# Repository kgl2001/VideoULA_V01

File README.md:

# VideoULA V01 — BBC Micro Video ULA Replacement
## 44-pin Xilinx XC9572XL CPLD Version

This repository contains the hardware design and firmware for the VideoULA V01, a drop-in replacement for the VC2069 Video ULA (IC6) in the Acorn BBC Micro Model B.

---

## Project Overview

The original BBC Micro Video ULA (IC6) is a custom ASIC that is no longer manufactured. Failed or missing ULAs result in a non-functional machine. This project provides a modern replacement using a CPLD and a small external SRAM for palette storage.

There are three hardware versions of this replacement, each in a separate repository:

| Version | CPLD | Macrocells | Tool | Repository |
|---|---|---|---|---|
| **V01** | Xilinx XC9572XL-10-VQ44 | 72 | ISE 14.7 | This repo |
| V02 | Xilinx XC9572XL-10-VQ64 | 72 | ISE 14.7 | [VideoULA_V02](https://github.com/kgl2001/VideoULA_V02) |
| V03 | Atmel ATF1504AS-10AU44 | 64 | Quartus 13.0 SP1 | [VideoULA_V03](https://github.com/kgl2001/VideoULA_V03) |

All three versions share the same 28-pin DIP footprint as the original ULA and are pin-compatible with the BBC Micro motherboard.

---

## V01 Hardware

- **CPLD**: Xilinx XC9572XL-10-VQ44 (72 macrocells, 3.3V core, 5V tolerant I/O)
- **SRAM**: ISSI IS62C256AL-45TLI (32K×8, 5V, TSOP-28, 45ns) — only locations 0-15 and bits 0-3 used
- **Oscillator**: 48MHz SMD oscillator (3225 package, 5V) — for 48MHz operating mode only
- **LDO**: XC6206P332MR (SOT-23, 3.3V) — powers CPLD core

### Hardware Revisions

| Revision | Status | Changes |
|---|---|---|
| Rev01 | Built and tested | Initial release |
| Rev02 | PCB designed, not yet built | Added 47Ω series resistor and 74LVC1G17 Schmitt trigger buffer on CLK_IN; CPLD pin assignments updated |
| Rev03 | PCB designed, not yet built | Added 74LV6T17 to buffer all clock outputs (8/4/2/1MHz, CRTC) for Master 128 compatibility |
| Rev04 | PCB designed, not yet built | Repositioned JTAG header |

Note: Only Rev01 has been built and tested. Rev02 onwards incorporate improvements identified during Rev01 testing.

### CLK_IN Reliability Daughterboard

During testing of Rev01 on BBC Micro machines with the original 16MHz clock circuit, some machines showed reliability issues in 16MHz operating mode — particularly on cold startup. Investigation revealed that the BBC's 16MHz crystal oscillator circuit produces a noisy clock signal that the CPLD occasionally misinterprets as spurious edges, causing display glitches.

To address this without waiting for a new PCB revision, a small standalone buffer board was developed. This daughterboard:

- Plugs into the BBC Micro motherboard in place of the VideoULA V01
- The VideoULA V01 then plugs into the daughterboard
- Intercepts the 16MHz clock signal from the BBC motherboard
- Passes it through a 47Ω series resistor and 74HCT14E Schmitt trigger buffer before it reaches the CPLD
- Passes all other signals through unchanged

The 74HCT14E was chosen as a through-hole part for ease of hand soldering. Rev02+ PCB designs use the smaller surface-mount 74LVC1G17 in conjunction with a series resistor to achieve the same signal conditioning in a more compact form.

This fix was confirmed to resolve the cold startup reliability issues on affected machines. The improvement has been incorporated into Rev02 of the V01 PCB and all subsequent hardware versions.

The daughterboard design files are included in this repository.

---

## Firmware

The firmware is written in Verilog and built using Xilinx ISE 14.7.

### Operating Modes

Two firmware builds are required — one per operating mode. To switch modes, reprogram the CPLD with the appropriate `.jed` file. A solder bridge on the PCB selects whether the 48MHz oscillator or the BBC's 16MHz clock is connected to the CPLD clock input.

#### 48MHz Mode (recommended)
- Uses the onboard 48MHz oscillator as the master clock
- Generates all BBC clock outputs (8/4/2/1MHz, CRTC, 6MHz) internally
- Provides clean, phase-locked 6MHz output for the SAA5050 teletext chip (tD ≈ 20ns ✓)
- Works reliably on all machines from cold power-up, including those with noisy clock circuits
- Build: uncomment `` `define CLK_48MHZ `` in `VideoULA.v`

#### 16MHz Mode
- Uses the BBC motherboard's 16MHz clock as the master clock
- No onboard oscillator required
- May show brief display noise on cold startup on machines with noisy 16MHz clock circuits
- The CLK_IN daughterboard resolves this on Rev01; Rev02+ has the fix built in
- Build: uncomment `` `define CLK_16MHZ `` in `VideoULA.v`

### ISE Fitter Settings (critical)

| Setting | Value | Notes |
|---|---|---|
| Implementation Template | **Optimise Speed** | Density causes timing failures at temperature |
| Macrocell Power | **Std** | Low Power prevents BBC from booting |
| Output Slew Rate | Fast | |
| Default Powerup Value | Low | |
| Pterms | **14** (16MHz build only) | Default 25 causes silent fit failure in 16MHz build |

### Build Instructions

1. Open Xilinx ISE 14.7
2. Create a new project targeting `XC9572XL-10-VQ44`
3. Add `src/VideoULA.v` and `src/VideoULA.ucf` to the project
4. Select the operating mode by uncommenting the appropriate `define` in `VideoULA.v`
5. Set fitter options as above
6. Run `Implement Design` to generate the `.jed` file
7. Program the CPLD using iMPACT or a compatible JTAG programmer

---

## SRAM Wiring

The external SRAM stores the 16-entry colour palette (4 bits per entry):

| SRAM Pin | Connection |
|---|---|
| A0-A3 | CPLD SRAM_ADDR[0:3] |
| A4-A14 | GND (tie low) |
| D0-D3 | CPLD SRAM_DATA[0:3] (bidirectional) |
| D4-D7 | Leave unconnected |
| /WE | CPLD SRAM_nWE |
| /OE | GND (always output enabled) |
| /CS | GND (always selected) |

---

## 6MHz Clock for Mode 7 (Teletext)

The SAA5050 teletext chip requires a 6MHz clock with a specific phase relationship to the 1MHz system clock (tD = 6-60ns from 6MHz rising edge to 1MHz falling edge).

- **48MHz mode**: The CPLD generates a clean, phase-locked 6MHz output on the CLK_6M pin (tD ≈ 20ns ✓). This can be connected to the SAA5050 via an IC37 replacement board.
- **16MHz mode**: The BBC motherboard's existing 6MHz generation circuit is used. The CPLD CLK_6M output is held high-Z.

---

## PCB Design Notes

The PCB has been designed using KiCAD V10 as a 2-layer board. It can easily be changed to a 4-layer board with GND/Power planes on the inner layers if signal integrity is a concern.

### JLCPCB Fabrication

The board design includes a 5×5mm silkscreen box on the underside of the PCB. This is used by JLCPCB to position a QR code serial number. When ordering from JLCPCB:

- Select **Specify position** in the QR code / 2D barcode options during the ordering process
- If this option is not selected, JLCPCB will print the 5×5mm silkscreen box as-is and attempt to place the QR code at a different location of their choosing

If not using JLCPCB, the chosen fabricator will likely print the 5×5mm box as a plain white square on the PCB. To avoid this, remove the silkscreen box from the PCB design and regenerate the Gerber files before submitting.

### Assembly

A combined CPL (Component Placement List) and BOM (Bill of Materials) Excel file is included in the Gerbers folder. This can be used directly with the JLCPCB PCBA (PCB Assembly) service.

Note that the JLCPCB Economy PCBA process only assembles components on one side of the PCB. Select the **top side** for assembly — this leaves only the SRAM and its associated decoupling capacitor to be hand soldered to the underside of the board.

---

## Known Limitations

- **Cold startup noise (16MHz mode, standard clock machines)**: Machines with noisy 16MHz clock circuits may show brief display noise on cold power-up. Use the CLK_IN daughterboard (Rev01) or upgrade to Rev02+ which has the fix built in. The 48MHz operating mode is not affected.
- **Master 128 compatibility**: V01 has not been tested on the Master 128. Clock output buffering (added in Rev03) may be required for full Master 128 compatibility.
- **SCART/HDMI adapter compatibility**: Some SCART→HDMI display adapters may show minor pixel artefacts with non-standard screen modes. RGBtoHDMI and direct CRT connections are not affected.

---

## Compatibility

Tested on BBC Micro Model B with original clock circuit and with clock fixer modification. Not tested on BBC Master 128.

---

## Credits

- **Ken Lowe** — PCB design, Verilog development and testing
- **hoglet (Stardot forums)** — Clock architecture analysis, DRAM timing analysis, community testing
- **Stardot community** — Testing, feedback and suggestions

---

## Licence

Hardware: [Creative Commons BY-SA 4.0](https://creativecommons.org/licenses/by-sa/4.0/)

Firmware: [MIT Licence](https://opensource.org/licenses/MIT)

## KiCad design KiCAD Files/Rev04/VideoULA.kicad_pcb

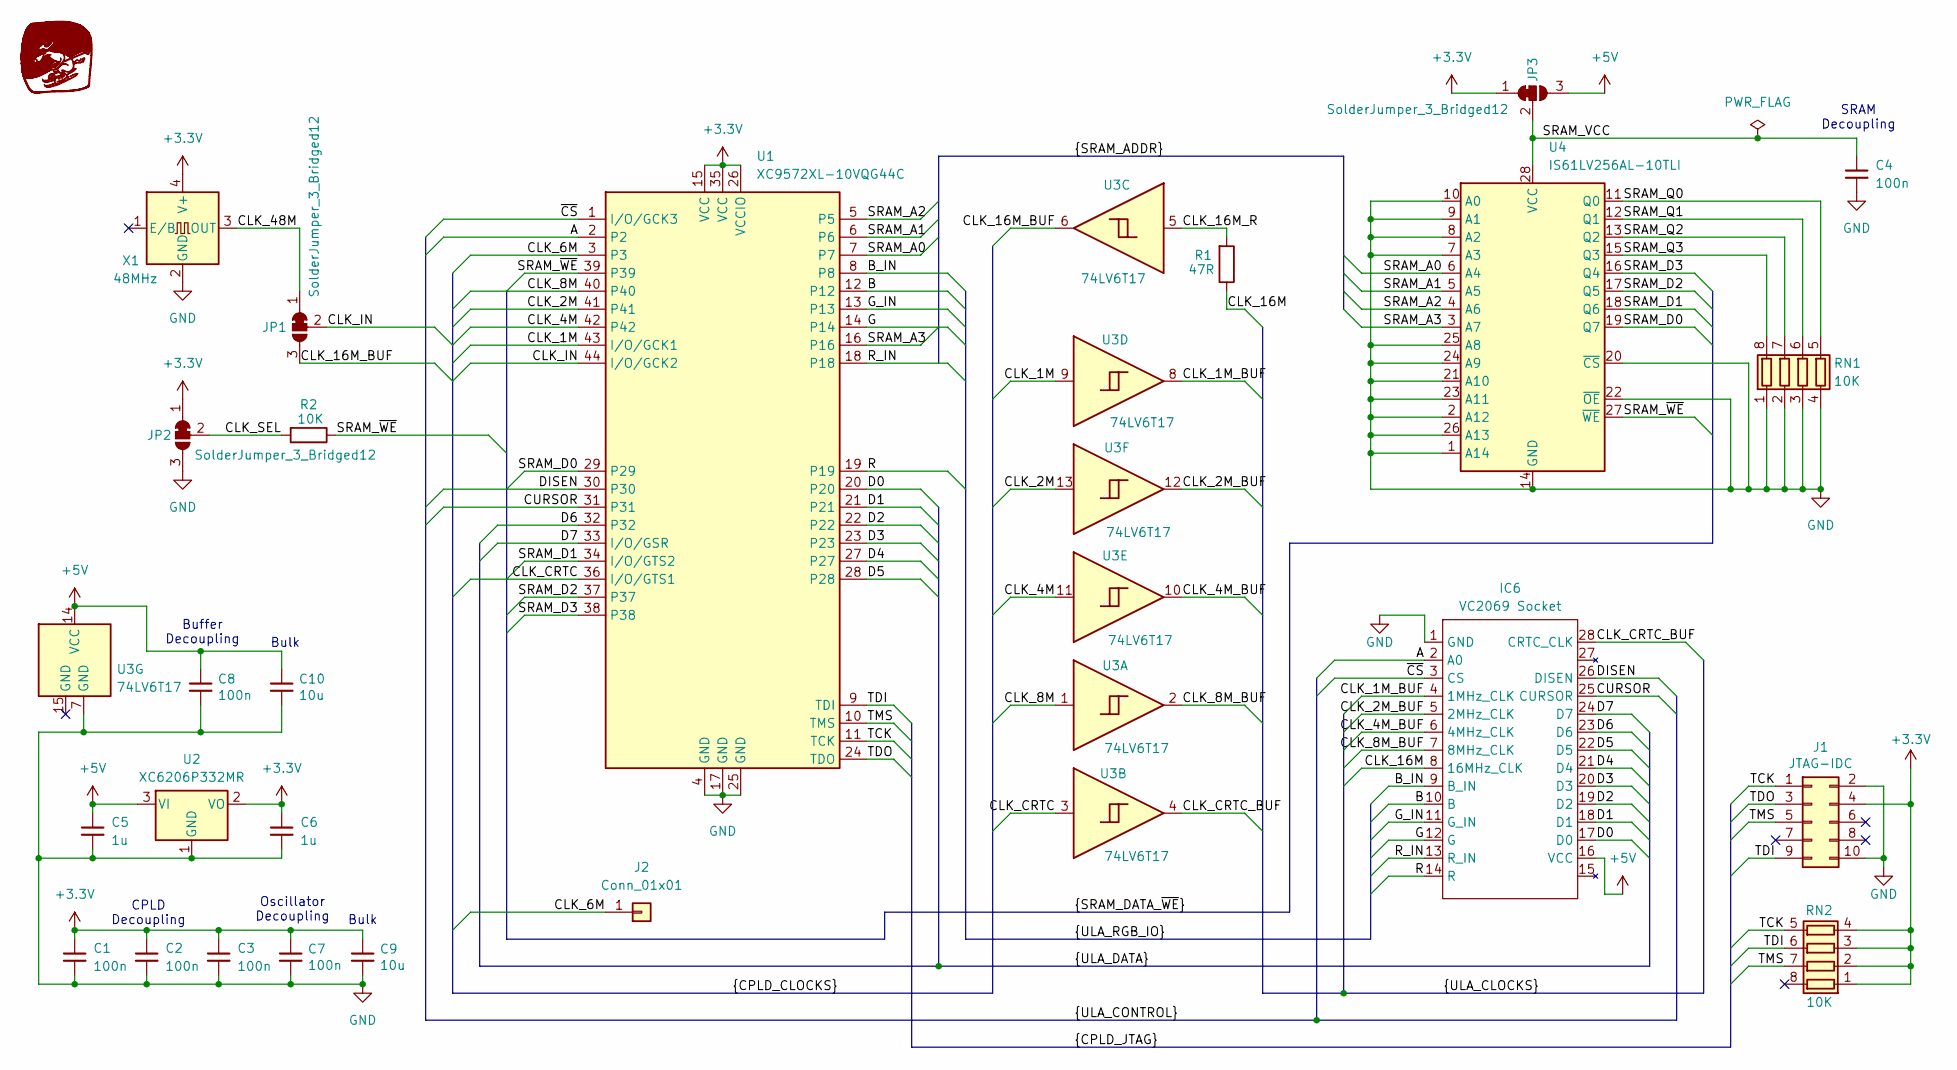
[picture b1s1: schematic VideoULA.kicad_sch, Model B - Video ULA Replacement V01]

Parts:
C1, C2, C3, C4, C7, C8: 100n; C_0603_1608Metric; JLC Part Number C14663
C5, C6: 1u; C_0603_1608Metric; JLC Part Number C15849
C9, C10: 10u; C_0603_1608Metric; JLC Part Number C19702
G1: Skidog; skidog_inv
IC6: VC2069 Socket; DIP-28_W15.24mm
J1: JTAG-IDC; PinHeader_2x05_P2.54mm_Vertical
J2: Conn_01x01; PinHeader_1x01_P2.54mm_Horizontal
JP1, JP2, JP3: SolderJumper_3_Bridged12; SolderJumper-3_P1.3mm_Bridged12_RoundedPad1.0x1.5mm
R1: 47R; R_0603_1608Metric; JLC Part Number C23182
R2: 10K; R_0603_1608Metric; JLC Part Number C25804
RN1, RN2: 10K; R_Array_Convex_4x0603; JLC Part Number C29718
U1: XC9572XL-10VQG44C; LQFP-44_10x10mm_P0.8mm; JLC Part Number C569042
U2: XC6206P332MR; SOT-23-3; JLC Part Number C5446
U3: 74LV6T17; DHWQFN-14-1EP_2.5x3mm_P0.5mm_EP1x1.5mm_ThermalVias; JLC Part Number C22428345
U4: IS61LV256AL-10TLI; TSOP-I-28_11.8x8mm_P0.55mm_SRAM; JLC Part Number C2062662
X1: 48MHz; Oscillator_SMD_Yajingxin_TFOM48M4RHKCNT2T-4Pin_3.2x2.5mm; JLC Part Number C454614

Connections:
+3.3V: C1.1, C2.1, C3.1, C6.1, C7.1, C9.1, J1.4, JP2.1 (A), JP3.1 (A), RN2.1 (R1.1), RN2.2 (R2.1), RN2.3 (R3.1), RN2.4 (R4.1), U1.15 (VCC), U1.26 (VCCIO), U1.35 (VCC), U2.2 (VO), X1.4 (V+)
+5V: C5.1, C8.1, C10.1, IC6.16 (VCC), JP3.3 (B), U2.3 (VI), U3.14 (VCC)
/A: IC6.2 (A0), U1.2
/B: IC6.10 (B), U1.12
/B_IN: IC6.9 (B_IN), U1.8
/CLK_1M: U1.43 (I/O/GCK1), U3.9
/CLK_1M_BUF: IC6.4 (1MHz_CLK), U3.8
/CLK_2M: U1.41, U3.13
/CLK_2M_BUF: IC6.5 (2MHz_CLK), U3.12
/CLK_4M: U1.42, U3.11
/CLK_4M_BUF: IC6.6 (4MHz_CLK), U3.10
/CLK_6M: J2.1 (Pin_1_1), U1.3
/CLK_8M: U1.40, U3.1
/CLK_8M_BUF: IC6.7 (8MHz_CLK), U3.2
/CLK_16M: IC6.8 (16MHz_CLK), R1.1
/CLK_16M_BUF: JP1.3 (B), U3.6
/CLK_16M_R: R1.2, U3.5
/CLK_48M: JP1.1 (A), X1.3 (OUT)
/CLK_CRTC: U1.36 (I/O/GTS1), U3.3
/CLK_CRTC_BUF: IC6.28 (CRTC_CLK), U3.4
/CLK_IN: JP1.2 (C), U1.44 (I/O/GCK2)
/CLK_SEL: JP2.2 (C), R2.2
/CURSOR: IC6.25 (CURSOR), U1.31
/D0: IC6.17 (D0), U1.20
/D1: IC6.18 (D1), U1.21
/D2: IC6.19 (D2), U1.22
/D3: IC6.20 (D3), U1.23
/D4: IC6.21 (D4), U1.27
/D5: IC6.22 (D5), U1.28
/D6: IC6.23 (D6), U1.32
/D7: IC6.24 (D7), U1.33 (I/O/GSR)
/DISEN: IC6.26 (DISEN), U1.30
/G: IC6.12 (G), U1.14
/G_IN: IC6.11 (G_IN), U1.13
/R: IC6.14 (R), U1.19
/R_IN: IC6.13 (R_IN), U1.18
/SRAM_A0: U1.7, U4.6 (A4)
/SRAM_A1: U1.6, U4.5 (A5)
/SRAM_A2: U1.5, U4.4 (A6)
/SRAM_A3: U1.16, U4.3 (A7)
/SRAM_D0: U1.29, U4.19 (Q7)
/SRAM_D1: U1.34 (I/O/GTS2), U4.18 (Q6)
/SRAM_D2: U1.37, U4.17 (Q5)
/SRAM_D3: U1.38, U4.16 (Q4)
/SRAM_Q0: RN1.5 (R4.2), U4.11 (Q0)
/SRAM_Q1: RN1.6 (R3.2), U4.12 (Q1)
/SRAM_Q2: RN1.7 (R2.2), U4.13 (Q2)
/SRAM_Q3: RN1.8 (R1.2), U4.15 (Q3)
/SRAM_VCC: C4.1, JP3.2 (C), U4.28 (VCC)
/SRAM_~WE: R2.1, U1.39, U4.27 (~WE)
/TCK: J1.1, RN2.5 (R4.2), U1.11 (TCK)
/TDI: J1.9, RN2.6 (R3.2), U1.9 (TDI)
/TDO: J1.3, U1.24 (TDO)
/TMS: J1.5, RN2.7 (R2.2), U1.10 (TMS)
/~CS: IC6.3 (CS), U1.1 (I/O/GCK3)
GND: C1.2, C2.2, C3.2, C4.2, C5.2, C6.2, C7.2, C8.2, C9.2, C10.2, IC6.1 (GND), J1.2, J1.10, JP2.3 (B), RN1.1 (R1.1), RN1.2 (R2.1), RN1.3 (R3.1), RN1.4 (R4.1), U1.4 (GND), U1.17 (GND), U1.25 (GND), U2.1 (GND), U3.7 (GND), U4.1 (A14), U4.2 (A12), U4.7 (A3), U4.8 (A2), U4.9 (A1), U4.10 (A0), U4.14 (GND), U4.20 (~CS), U4.21 (A10), U4.22 (~OE), U4.23 (A11), U4.24 (A9), U4.25 (A8), U4.26 (A13), X1.2 (GND)

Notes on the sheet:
SRAM Decoupling
Oscillator Decoupling
CPLD Decoupling
Bulk
Buffer Decoupling

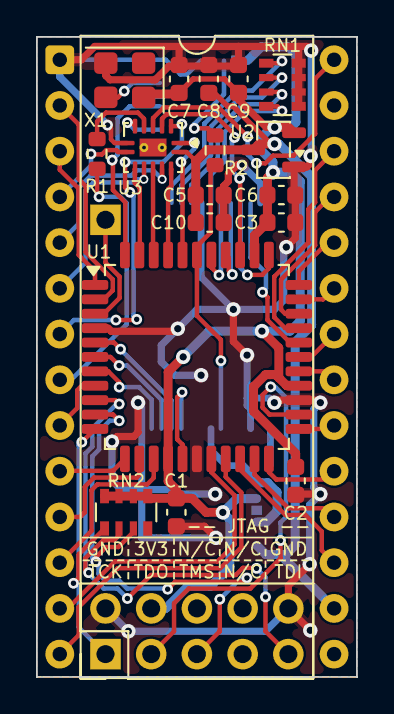
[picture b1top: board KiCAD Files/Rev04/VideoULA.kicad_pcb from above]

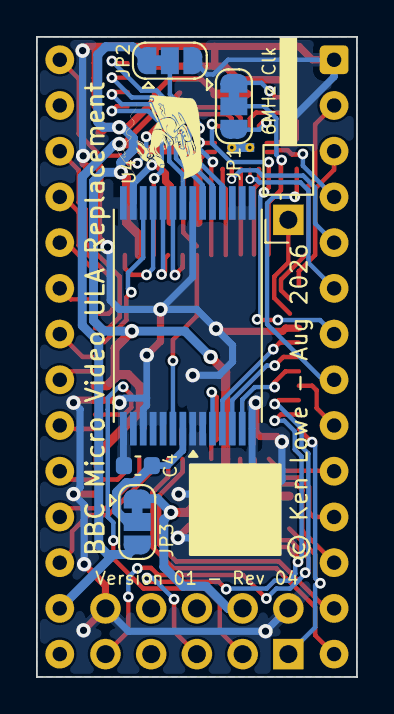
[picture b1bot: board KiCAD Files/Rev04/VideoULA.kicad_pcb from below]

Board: 2 copper layers, 17.8 x 35.6 mm, 26 parts (7 on the bottom side), 56 nets.

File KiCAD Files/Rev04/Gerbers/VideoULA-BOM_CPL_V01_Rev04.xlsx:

Designator | Val | Package | Mid X | Mid Y | Rotation | Layer | JLC Part Number
C4 | 100n | C_0603_1608Metric | 88.882531999999998 | -62.421548000000001 | 0 | bottom | C14663
U4 | IS61LV256AL-10TLI | TSOP-I-28_11.8x8mm_P0.55mm_SRAM | 86.111000000000004 | -54.097000000000001 | 90 | bottom | C2062662
C1 | 100n | C_0603_1608Metric | 84.46 | -65.013999999999996 | -90 | top | C14663
C2 | 100n | C_0603_1608Metric | 91.089731999999998 | -63.266348000000001 | -90 | top | C14663
C3 | 100n | C_0603_1608Metric | 90.293999999999997 | -48.915399999999998 | 0 | top | C14663
C5 | 1u | C_0603_1608Metric | 86.3142 | -47.391399999999997 | 0 | top | C15849
C6 | 1u | C_0603_1608Metric | 90.293999999999997 | -47.391399999999997 | 0 | top | C15849
C7 | 100n | C_0603_1608Metric | 84.612399999999994 | -40.939799999999998 | 90 | top | C14663
C8 | 100n | C_0603_1608Metric | 86.2624 | -40.939799999999998 | 90 | top | C14663
C9 | 10u | C_0603_1608Metric | 87.912400000000005 | -40.939799999999998 | 90 | top | C19702
C10 | 10u | C_0603_1608Metric | 86.3142 | -48.915399999999998 | 0 | top | C19702
R1 | 47R | R_0603_1608Metric | 80.0578 | -45.105400000000003 | 90 | top | C23182
R2 | 10K | R_0603_1608Metric | 86.611000000000004 | -44.902200000000001 | 90 | top | C25804
RN1 | 10K | R_Array_Convex_4x0603 | 90.355732000000003 | -41.263348000000001 | -90 | top | C29718
RN2 | 10K | R_Array_Convex_4x0603 | 81.672399999999996 | -65.013999999999996 | 0 | top | C29718
U1 | XC9572XL-10VQG44C | LQFP-44_10x10mm_P0.8mm | 85.602999999999994 | -56.383000000000003 | -90 | top | C569042
U2 | XC6206P332MR | SOT-23-3 | 89.862200000000001 | -44.876800000000003 | 0 | top | C5446
U3 | 74LV6T17 | DHWQFN-14-1EP_2.5x3mm_P0.5mm_EP1x1.5mm_ThermalVias | 83.164599999999993 | -44.7498 | -90 | top | C22428345
X1 | 48MHz | Oscillator_SMD_Yajingxin_TFOM48M4RHKCNT2T-4Pin_3.2x2.5mm | 81.592731999999998 | -41.009348000000003 | 180 | top | C454614

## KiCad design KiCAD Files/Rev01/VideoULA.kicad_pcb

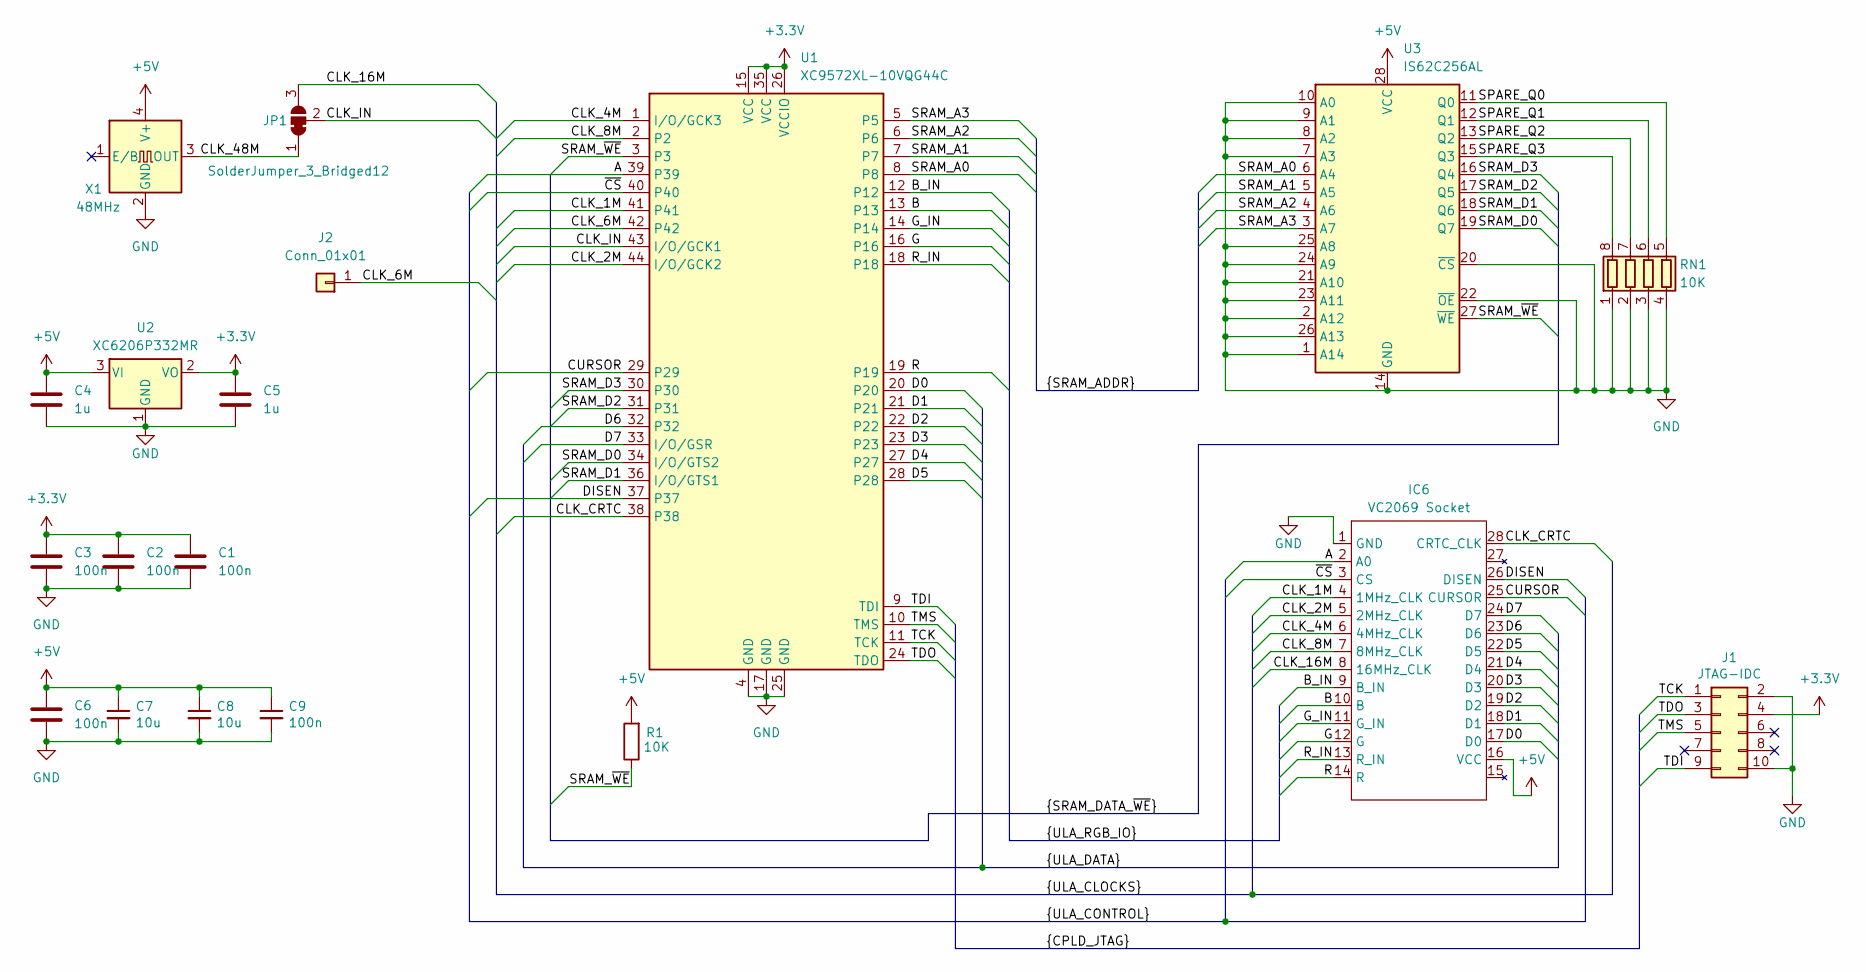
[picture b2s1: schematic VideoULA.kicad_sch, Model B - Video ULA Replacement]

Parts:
C1, C2, C3, C6, C9: 100n; C_0603_1608Metric; JLC Part Number C14663
C4, C5: 1u; C_0603_1608Metric; JLC Part Number C15849
C7, C8: 10u; C_0603_1608Metric; JLC Part Number C19702
IC6: VC2069 Socket; DIP-28_W15.24mm
J1: JTAG-IDC; PinHeader_2x05_P2.54mm_Vertical
J2: Conn_01x01; PinHeader_1x01_P2.54mm_Horizontal
JP1: SolderJumper_3_Bridged12; SolderJumper-3_P1.3mm_Bridged12_RoundedPad1.0x1.5mm
R1: 10K; R_0603_1608Metric; JLC Part Number C25804
RN1: 10K; R_Array_Convex_4x0603; JLC Part Number C29718
U1: XC9572XL-10VQG44C; LQFP-44_10x10mm_P0.8mm; JLC Part Number C569042
U2: XC6206P332MR; SOT-23-3; JLC Part Number C5446
U3: IS62C256AL; TSOP-I-28_11.8x8mm_P0.55mm_SRAM; JLC Part Number C47143
X1: 48MHz; Oscillator_SMD_Yajingxin_TFOM48M4RHKCNT2T-4Pin_3.2x2.5mm; JLC Part Number C454614

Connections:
+3.3V: C1.1, C2.1, C3.1, C5.1, J1.4, U1.15 (VCC), U1.26 (VCCIO), U1.35 (VCC), U2.2 (VO)
+5V: C4.1, C6.1, C7.1, C8.1, C9.1, IC6.16 (VCC), R1.2, U2.3 (VI), U3.28 (VCC), X1.4 (V+)
/A: IC6.2 (A0), U1.39
/B: IC6.10 (B), U1.13
/B_IN: IC6.9 (B_IN), U1.12
/CLK_1M: IC6.4 (1MHz_CLK), U1.41
/CLK_2M: IC6.5 (2MHz_CLK), U1.44 (I/O/GCK2)
/CLK_4M: IC6.6 (4MHz_CLK), U1.1 (I/O/GCK3)
/CLK_6M: J2.1 (Pin_1_1), U1.42
/CLK_8M: IC6.7 (8MHz_CLK), U1.2
/CLK_16M: IC6.8 (16MHz_CLK), JP1.3 (B)
/CLK_48M: JP1.1 (A), X1.3 (OUT)
/CLK_CRTC: IC6.28 (CRTC_CLK), U1.38
/CLK_IN: JP1.2 (C), U1.43 (I/O/GCK1)
/CURSOR: IC6.25 (CURSOR), U1.29
/D0: IC6.17 (D0), U1.20
/D1: IC6.18 (D1), U1.21
/D2: IC6.19 (D2), U1.22
/D3: IC6.20 (D3), U1.23
/D4: IC6.21 (D4), U1.27
/D5: IC6.22 (D5), U1.28
/D6: IC6.23 (D6), U1.32
/D7: IC6.24 (D7), U1.33 (I/O/GSR)
/DISEN: IC6.26 (DISEN), U1.37
/G: IC6.12 (G), U1.16
/G_IN: IC6.11 (G_IN), U1.14
/R: IC6.14 (R), U1.19
/R_IN: IC6.13 (R_IN), U1.18
/SPARE_Q0: RN1.5 (R4.2), U3.11 (Q0)
/SPARE_Q1: RN1.6 (R3.2), U3.12 (Q1)
/SPARE_Q2: RN1.7 (R2.2), U3.13 (Q2)
/SPARE_Q3: RN1.8 (R1.2), U3.15 (Q3)
/SRAM_A0: U1.8, U3.6 (A4)
/SRAM_A1: U1.7, U3.5 (A5)
/SRAM_A2: U1.6, U3.4 (A6)
/SRAM_A3: U1.5, U3.3 (A7)
/SRAM_D0: U1.34 (I/O/GTS2), U3.19 (Q7)
/SRAM_D1: U1.36 (I/O/GTS1), U3.18 (Q6)
/SRAM_D2: U1.31, U3.17 (Q5)
/SRAM_D3: U1.30, U3.16 (Q4)
/SRAM_~WE: R1.1, U1.3, U3.27 (~WE)
/TCK: J1.1, U1.11 (TCK)
/TDI: J1.9, U1.9 (TDI)
/TDO: J1.3, U1.24 (TDO)
/TMS: J1.5, U1.10 (TMS)
/~CS: IC6.3 (CS), U1.40
GND: C1.2, C2.2, C3.2, C4.2, C5.2, C6.2, C7.2, C8.2, C9.2, IC6.1 (GND), J1.2, J1.10, RN1.1 (R1.1), RN1.2 (R2.1), RN1.3 (R3.1), RN1.4 (R4.1), U1.4 (GND), U1.17 (GND), U1.25 (GND), U2.1 (GND), U3.1 (A14), U3.2 (A12), U3.7 (A3), U3.8 (A2), U3.9 (A1), U3.10 (A0), U3.14 (GND), U3.20 (~CS), U3.21 (A10), U3.22 (~OE), U3.23 (A11), U3.24 (A9), U3.25 (A8), U3.26 (A13), X1.2 (GND)

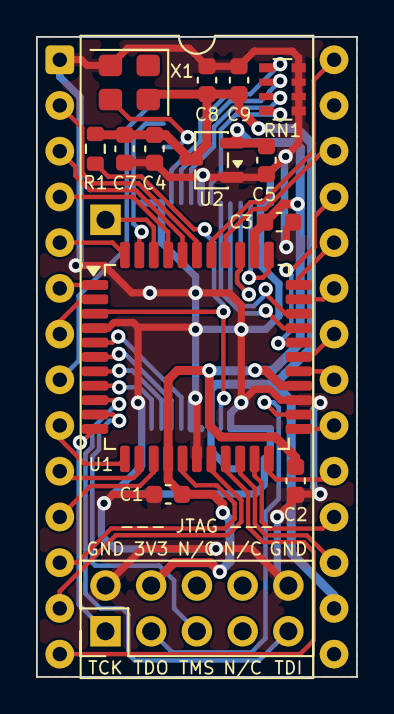
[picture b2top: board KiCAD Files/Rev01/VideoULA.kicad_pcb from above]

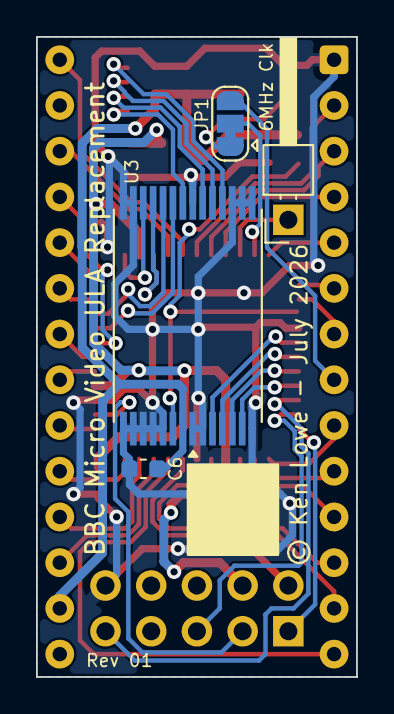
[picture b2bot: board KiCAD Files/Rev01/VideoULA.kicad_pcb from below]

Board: 2 copper layers, 17.8 x 35.6 mm, 19 parts (4 on the bottom side), 47 nets.

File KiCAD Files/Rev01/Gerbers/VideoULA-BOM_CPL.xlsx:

Designator | Val | Package | Mid X | Mid Y | Rotation | Layer | JLC Part Number
C6 | 100n | C_0603_1608Metric | 88.577731999999997 | -62.599347999999999 | 0 | bottom | C14663
U3 | IS62C256AL | TSOP-I-28_11.8x8mm_P0.55mm_SRAM | 86.111000000000004 | -54.097000000000001 | 90 | bottom | C47143
C1 | 100n | C_0603_1608Metric | 84.002799999999993 | -64.016347999999994 | 180 | top | C14663
C2 | 100n | C_0603_1608Metric | 91.089731999999998 | -63.266348000000001 | -90 | top | C14663
C3 | 100n | C_0603_1608Metric | 90.167000000000002 | -48.893999999999998 | 0 | top | C14663
C4 | 1u | C_0603_1608Metric | 83.243731999999994 | -44.819347999999998 | -90 | top | C15849
C5 | 1u | C_0603_1608Metric | 89.466731999999993 | -45.454348000000003 | -90 | top | C15849
C7 | 10n | C_0603_1608Metric | 81.584732000000002 | -44.819347999999998 | -90 | top | C57112
C8 | 10n | C_0603_1608Metric | 86.164732000000001 | -41.009348000000003 | 90 | top | C57112
C9 | 100n | C_0603_1608Metric | 87.942732000000007 | -41.009348000000003 | 90 | top | C14663
R1 | 10K | R_0603_1608Metric | 79.959131999999997 | -44.819347999999998 | 90 | top | C25804
RN1 | 10K | R_Array_Convex_4x0603 | 90.355732000000003 | -41.517347999999998 | 90 | top | C29718
U1 | XC9572XL-10VQG44C | LQFP-44_10x10mm_P0.8mm | 85.602999999999994 | -56.383000000000003 | 270 | top | C569042
U2 | XC6206P332MR | SOT-23-3 | 86.418732000000006 | -45.454348000000003 | 0 | top | C5446
X1 | 48MHz | Oscillator_SMD_Yajingxin_TFOM48M4RHKCNT2T-4Pin_3.2x2.5mm | 81.846732000000003 | -41.136347999999998 | 180 | top | C454614

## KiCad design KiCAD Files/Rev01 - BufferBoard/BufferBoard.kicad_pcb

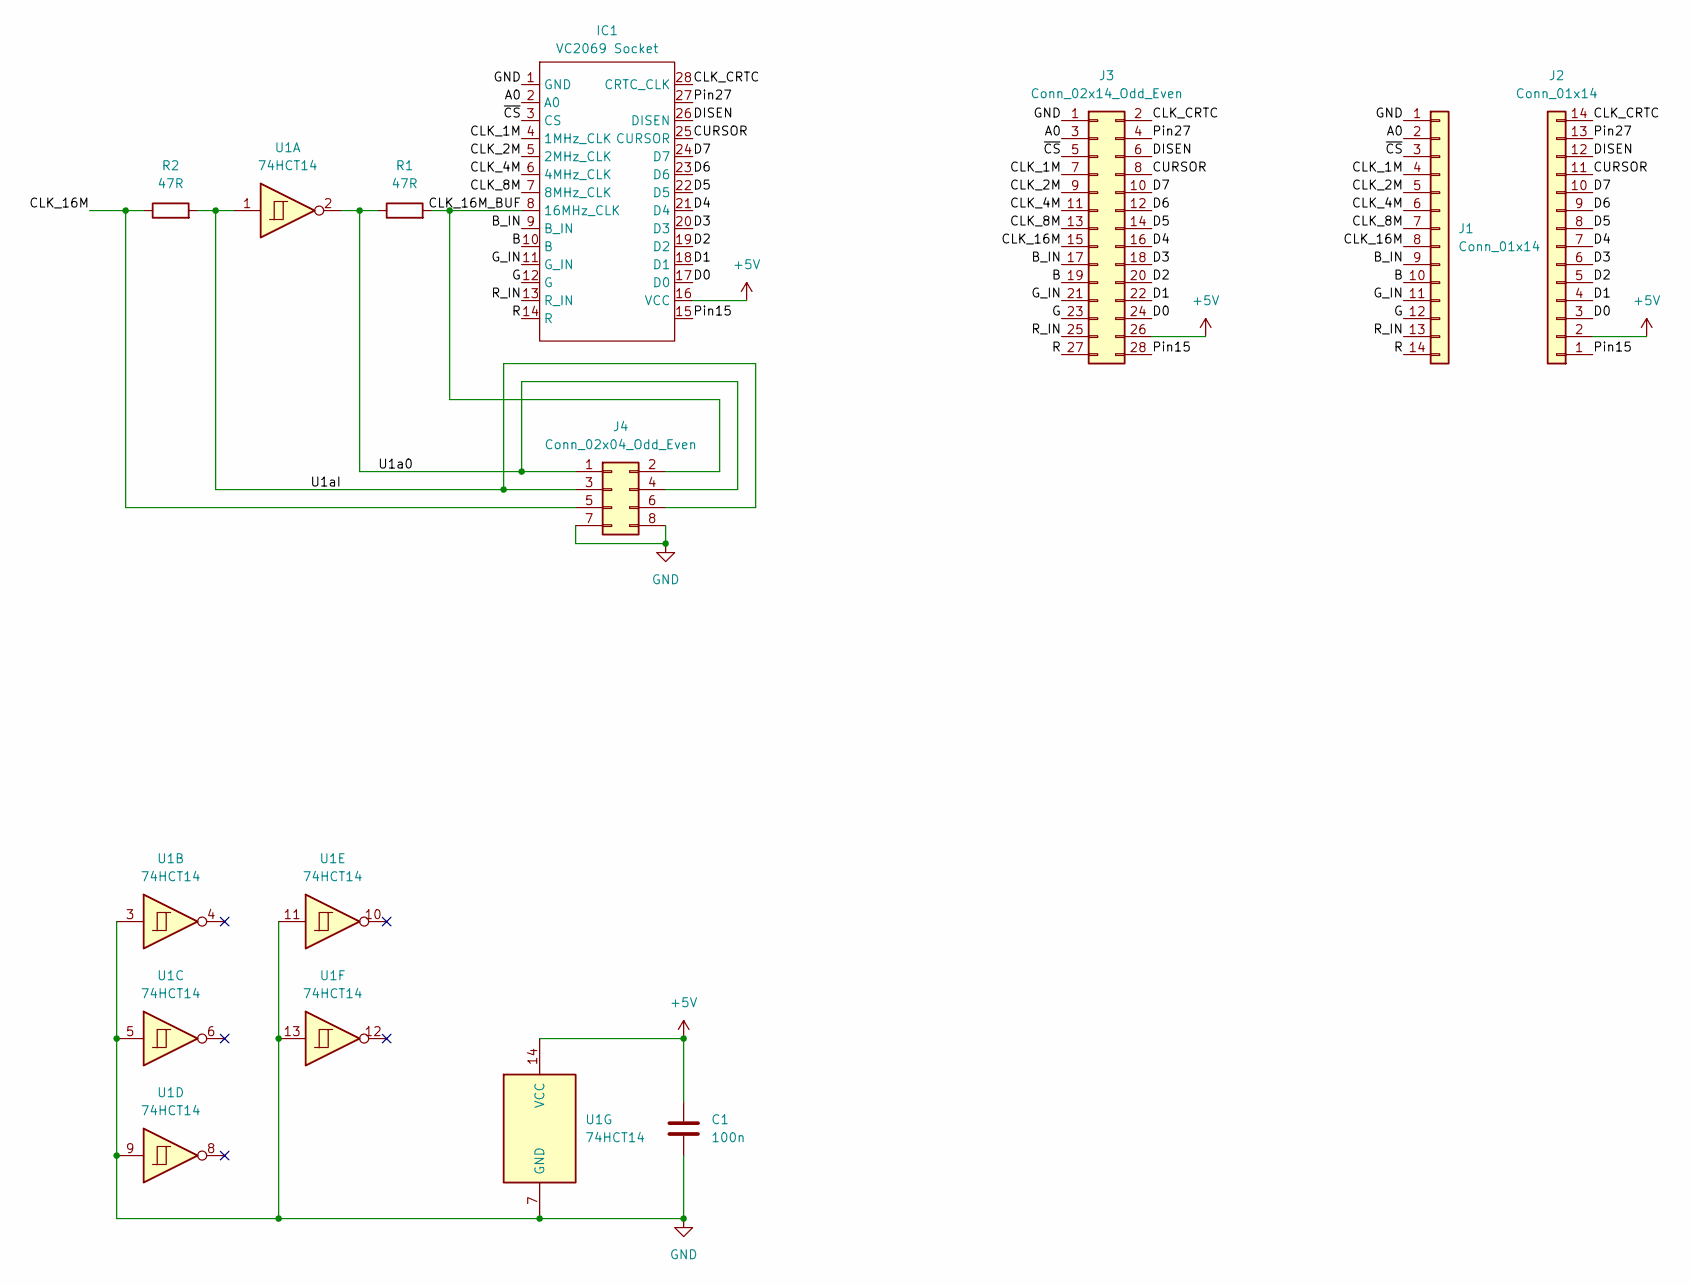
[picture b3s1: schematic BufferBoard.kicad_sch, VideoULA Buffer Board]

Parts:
C1: 100n; C_Disc_D4.3mm_W1.9mm_P5.00mm; JLC Part Number C14663
IC1: VC2069 Socket; DIP-28_W15.24mm_Socket
J1, J2: Conn_01x14; PinHeader_1x14_P2.54mm_Vertical
J3: Conn_02x14_Odd_Even; PinHeader_2x14_P2.54mm_Vertical
J4: Conn_02x04_Odd_Even; PinHeader_2x04_P2.54mm_Vertical
R1, R2: 47R; R_Axial_DIN0207_L6.3mm_D2.5mm_P10.16mm_Horizontal
U1: 74HCT14; DIP-14_W7.62mm_Socket

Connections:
+5V: C1.1, IC1.16 (VCC), J2.2, J3.26, U1.14 (VCC)
/A0: IC1.2 (A0), J1.2, J3.3
/B: IC1.10 (B), J1.10, J3.19
/B_IN: IC1.9 (B_IN), J1.9, J3.17
/CLK_1M: IC1.4 (1MHz_CLK), J1.4, J3.7
/CLK_2M: IC1.5 (2MHz_CLK), J1.5, J3.9
/CLK_4M: IC1.6 (4MHz_CLK), J1.6, J3.11
/CLK_8M: IC1.7 (8MHz_CLK), J1.7, J3.13
/CLK_16M: J1.8, J3.15, J4.5, R2.1
/CLK_16M_BUF: IC1.8 (16MHz_CLK), J4.2, R1.2
/CLK_CRTC: IC1.28 (CRTC_CLK), J2.14, J3.2
/CURSOR: IC1.25 (CURSOR), J2.11, J3.8
/D0: IC1.17 (D0), J2.3, J3.24
/D1: IC1.18 (D1), J2.4, J3.22
/D2: IC1.19 (D2), J2.5, J3.20
/D3: IC1.20 (D3), J2.6, J3.18
/D4: IC1.21 (D4), J2.7, J3.16
/D5: IC1.22 (D5), J2.8, J3.14
/D6: IC1.23 (D6), J2.9, J3.12
/D7: IC1.24 (D7), J2.10, J3.10
/DISEN: IC1.26 (DISEN), J2.12, J3.6
/G: IC1.12 (G), J1.12, J3.23
/G_IN: IC1.11 (G_IN), J1.11, J3.21
/Pin15: IC1.15, J2.1, J3.28
/Pin27: IC1.27, J2.13, J3.4
/R: IC1.14 (R), J1.14, J3.27
/R_IN: IC1.13 (R_IN), J1.13, J3.25
/U1a0: J4.1, J4.4, R1.1, U1.2
/U1aI: J4.3, J4.6, R2.2, U1.1
/~CS: IC1.3 (CS), J1.3, J3.5
GND: C1.2, IC1.1 (GND), J1.1, J3.1, J4.7, J4.8, U1.3, U1.5, U1.7 (GND), U1.9, U1.11, U1.13

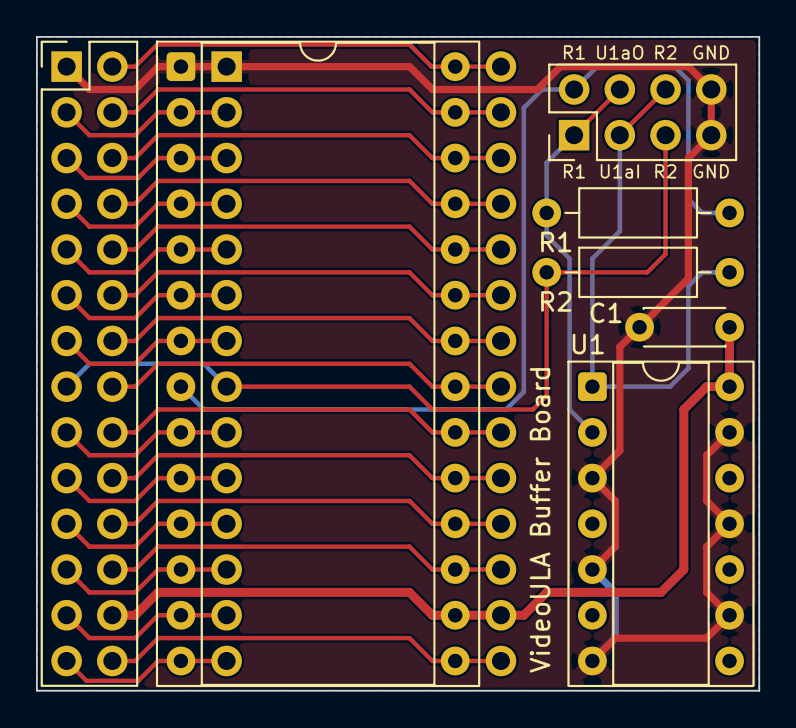
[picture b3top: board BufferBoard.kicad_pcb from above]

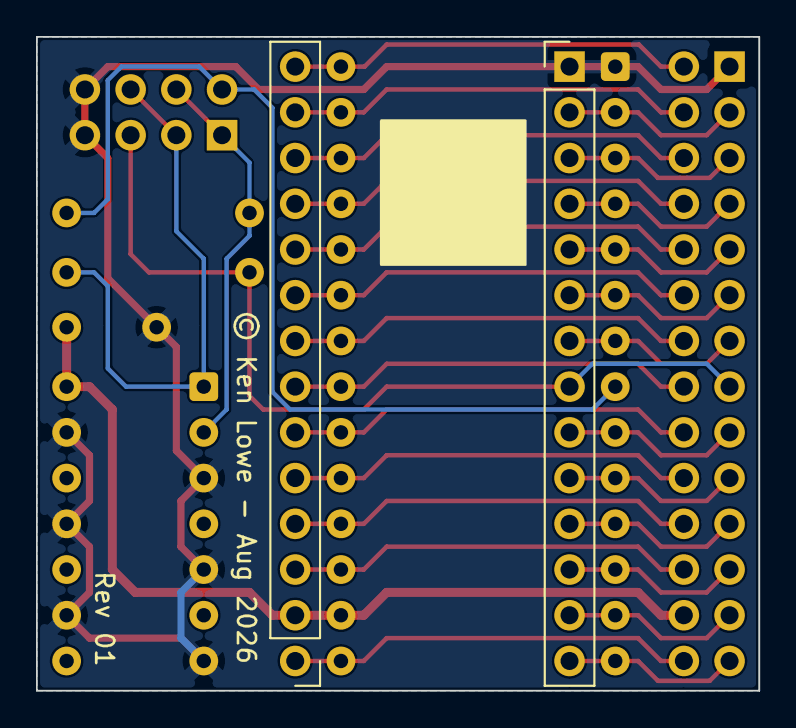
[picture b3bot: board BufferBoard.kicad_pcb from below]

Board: 2 copper layers, 40.1 x 36.3 mm, 9 parts (2 on the bottom side), 31 nets.

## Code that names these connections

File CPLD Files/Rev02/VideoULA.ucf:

# VideoULA V01 Rev02 - pin assignments (XC9572XL-VQ44)
# Derived from the KiCad schematic for hardware Rev02.
# CLK_6M: drives the SAA5050 in the 48MHz build only (high-Z in the 16MHz build).
NET "A"  LOC = "P42"  ;
NET "B"  LOC = "P12"  ;
NET "B_IN"  LOC = "P8"  ;
NET "CLK_1M"  LOC = "P40"  ;
NET "CLK_2M"  LOC = "P1"  ;
NET "CLK_4M"  LOC = "P2"  ;
NET "CLK_6M"  LOC = "P44"  ;
NET "CLK_8M"  LOC = "P3"  ;
NET "CLK_CRTC"  LOC = "P36"  ;
NET "CLK_IN"  LOC = "P43"  ;
NET "CURSOR"  LOC = "P31"  ;
NET "D<0>"  LOC = "P20"  ;
NET "D<1>"  LOC = "P21"  ;
NET "D<2>"  LOC = "P22"  ;
NET "D<3>"  LOC = "P23"  ;
NET "D<4>"  LOC = "P27"  ;
NET "D<5>"  LOC = "P28"  ;
NET "D<6>"  LOC = "P32"  ;
NET "D<7>"  LOC = "P33"  ;
NET "DISEN"  LOC = "P30"  ;
NET "G"  LOC = "P14"  ;
NET "G_IN"  LOC = "P13"  ;
NET "R"  LOC = "P19"  ;
NET "R_IN"  LOC = "P18"  ;
NET "SRAM_ADDR<0>"  LOC = "P7"  ;
NET "SRAM_ADDR<1>"  LOC = "P6"  ;
NET "SRAM_ADDR<2>"  LOC = "P5"  ;
NET "SRAM_ADDR<3>"  LOC = "P16"  ;
NET "SRAM_DATA<0>"  LOC = "P29"  ;
NET "SRAM_DATA<1>"  LOC = "P34"  ;
NET "SRAM_DATA<2>"  LOC = "P37"  ;
NET "SRAM_DATA<3>"  LOC = "P38"  ;
NET "SRAM_nWE"  LOC = "P39"  ;
NET "nCS"  LOC = "P41"  ;

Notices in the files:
KiCAD Files/Rev01 - BufferBoard/BufferBoard.kicad_pcb:
© Ken Lowe - Aug 2026
KiCAD Files/Rev01/VideoULA.kicad_pcb:
© Ken Lowe - July 2026
